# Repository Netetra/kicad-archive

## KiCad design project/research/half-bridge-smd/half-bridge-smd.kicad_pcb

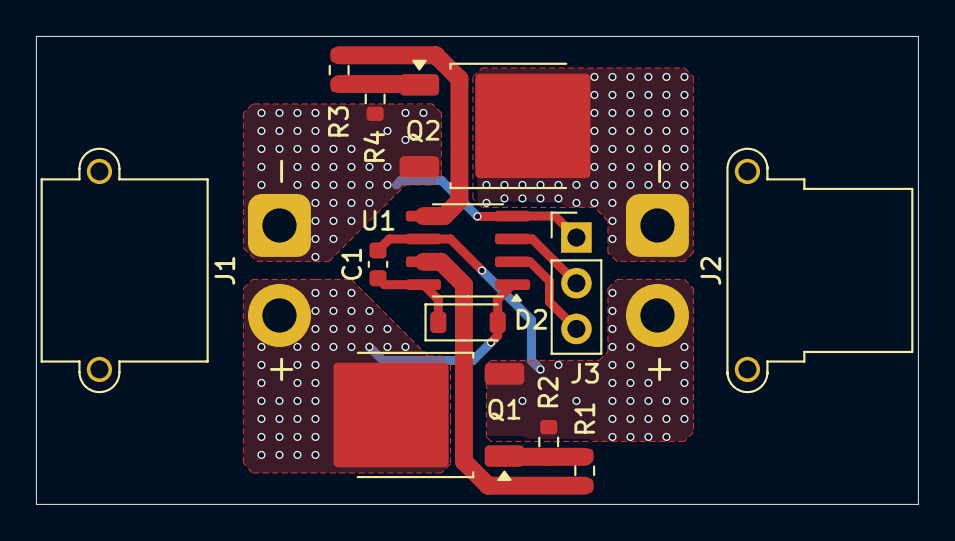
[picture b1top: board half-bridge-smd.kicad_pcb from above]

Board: 2 copper layers, 49.0 x 26.0 mm, 12 parts (0 on the bottom side), 11 nets.

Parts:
C1: 0.1uF; C_0603_1608Metric
D2: 1N4148W; D_SOD-123
J1: Power; AMASS_XT30PW-M_1x02_P2.50mm_Horizontal
J2: Output; AMASS_XT30PW-F_1x02_P2.50mm_Horizontal
J3: Input; PinHeader_1x03_P2.54mm_Vertical
Q1, Q2: TK25S06N1L; TO-252-2
R1, R3: 10Ω; R_0603_1608Metric
R2, R4: 10kΩ; R_0603_1608Metric
U1: IR2302; SOIC-8_3.9x4.9mm_P1.27mm

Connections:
+12V: D2.2 (A), J1.2, Q1.2 (D), U1.1 (VCC)
GND: J1.1, J3.1, Q2.3 (S), R4.2, U1.4 (COM)
unnamed: C1.1, D2.1 (K), U1.8 (VB)
unnamed: J2.1, Q2.2 (D)
unnamed: C1.2, J2.2, Q1.3 (S), R2.2, U1.6 (VS)
unnamed: J3.2, U1.3 (~SD)
unnamed: J3.3, U1.2 (IN)
unnamed: Q1.1 (G), R1.2, R2.1
unnamed: Q2.1 (G), R3.2, R4.1
unnamed: R1.1, U1.7 (HO)
unnamed: R3.1, U1.5 (LO)

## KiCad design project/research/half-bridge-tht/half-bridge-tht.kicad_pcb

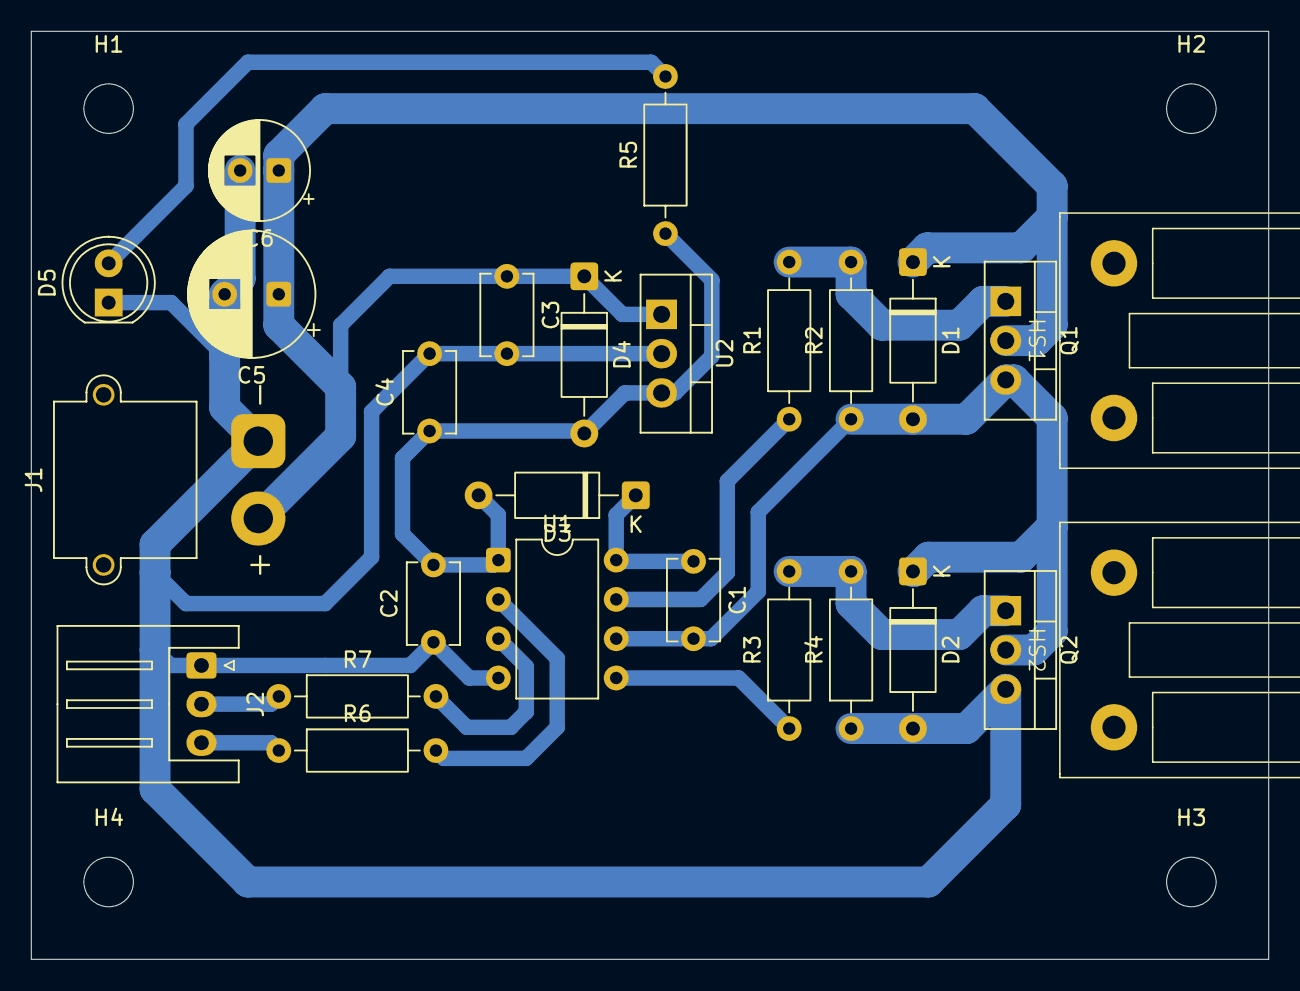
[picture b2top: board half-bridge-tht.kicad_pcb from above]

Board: 2 copper layers, 80.0 x 60.0 mm, 30 parts (0 on the bottom side), 14 nets.

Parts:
C1: 1uF; C_Disc_D5.1mm_W3.2mm_P5.00mm
C2, C4: 0.1uF; C_Disc_D5.1mm_W3.2mm_P5.00mm
C3: 0.47uF; C_Disc_D5.1mm_W3.2mm_P5.00mm
C5: 100uF; CP_Radial_D8.0mm_P3.50mm
C6: 47uF; CP_Radial_D6.3mm_P2.50mm
D1, D2, D3, D4: D; D_A-405_P10.16mm_Horizontal
D5: LED; LED_D5.0mm
H1, H2, H3, H4: MountingHole; MountingHole_3.2mm_M3
HS1, HS2: Heatsink; 16PB017
J1: Power; AMASS_XT30PW-M_1x02_P2.50mm_Horizontal
J2: Input; JST_XH_S3B-XH-A_1x03_P2.50mm_Horizontal
Q1, Q2: NMOS; TO-220-3_Vertical
R1, R3: 10Ω; R_Axial_DIN0207_L6.3mm_D2.5mm_P10.16mm_Horizontal
R2, R4, R5: 10kΩ; R_Axial_DIN0207_L6.3mm_D2.5mm_P10.16mm_Horizontal
R6, R7: 1kΩ; R_Axial_DIN0207_L6.3mm_D2.5mm_P10.16mm_Horizontal
U1: IR2302; DIP-8_W7.62mm
U2: L7812; TO-220-3_Vertical

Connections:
+12V: C2.2, C4.1, D3.2 (A), D4.2 (A), R5.1, U1.1 (VCC), U2.3 (OUT)
+BATT: C3.1, C5.1, C6.1, D1.1 (K), D4.1 (K), J1.2, Q1.2 (D), U2.1 (IN)
GND: C2.1, C3.2, C4.2, C5.2, C6.2, D2.2 (A), D5.1 (K), J1.1, J2.1, Q2.3 (S), R4.1, U1.4 (COM), U2.2 (GND)
unnamed: C1.2, D1.2 (A), D2.1 (K), Q1.3 (S), Q2.2 (D), R2.1, U1.6 (VS)
unnamed: C1.1, D3.1 (K), U1.8 (VB)
unnamed: D5.2 (A), R5.2
unnamed: J2.2, R7.1
unnamed: J2.3, R6.1
unnamed: Q1.1 (G), R1.2, R2.2
unnamed: Q2.1 (G), R3.2, R4.2
unnamed: R1.1, U1.7 (HO)
unnamed: R6.2, U1.2 (IN)
unnamed: R3.1, U1.5 (LO)
unnamed: R7.2, U1.3 (~SD)

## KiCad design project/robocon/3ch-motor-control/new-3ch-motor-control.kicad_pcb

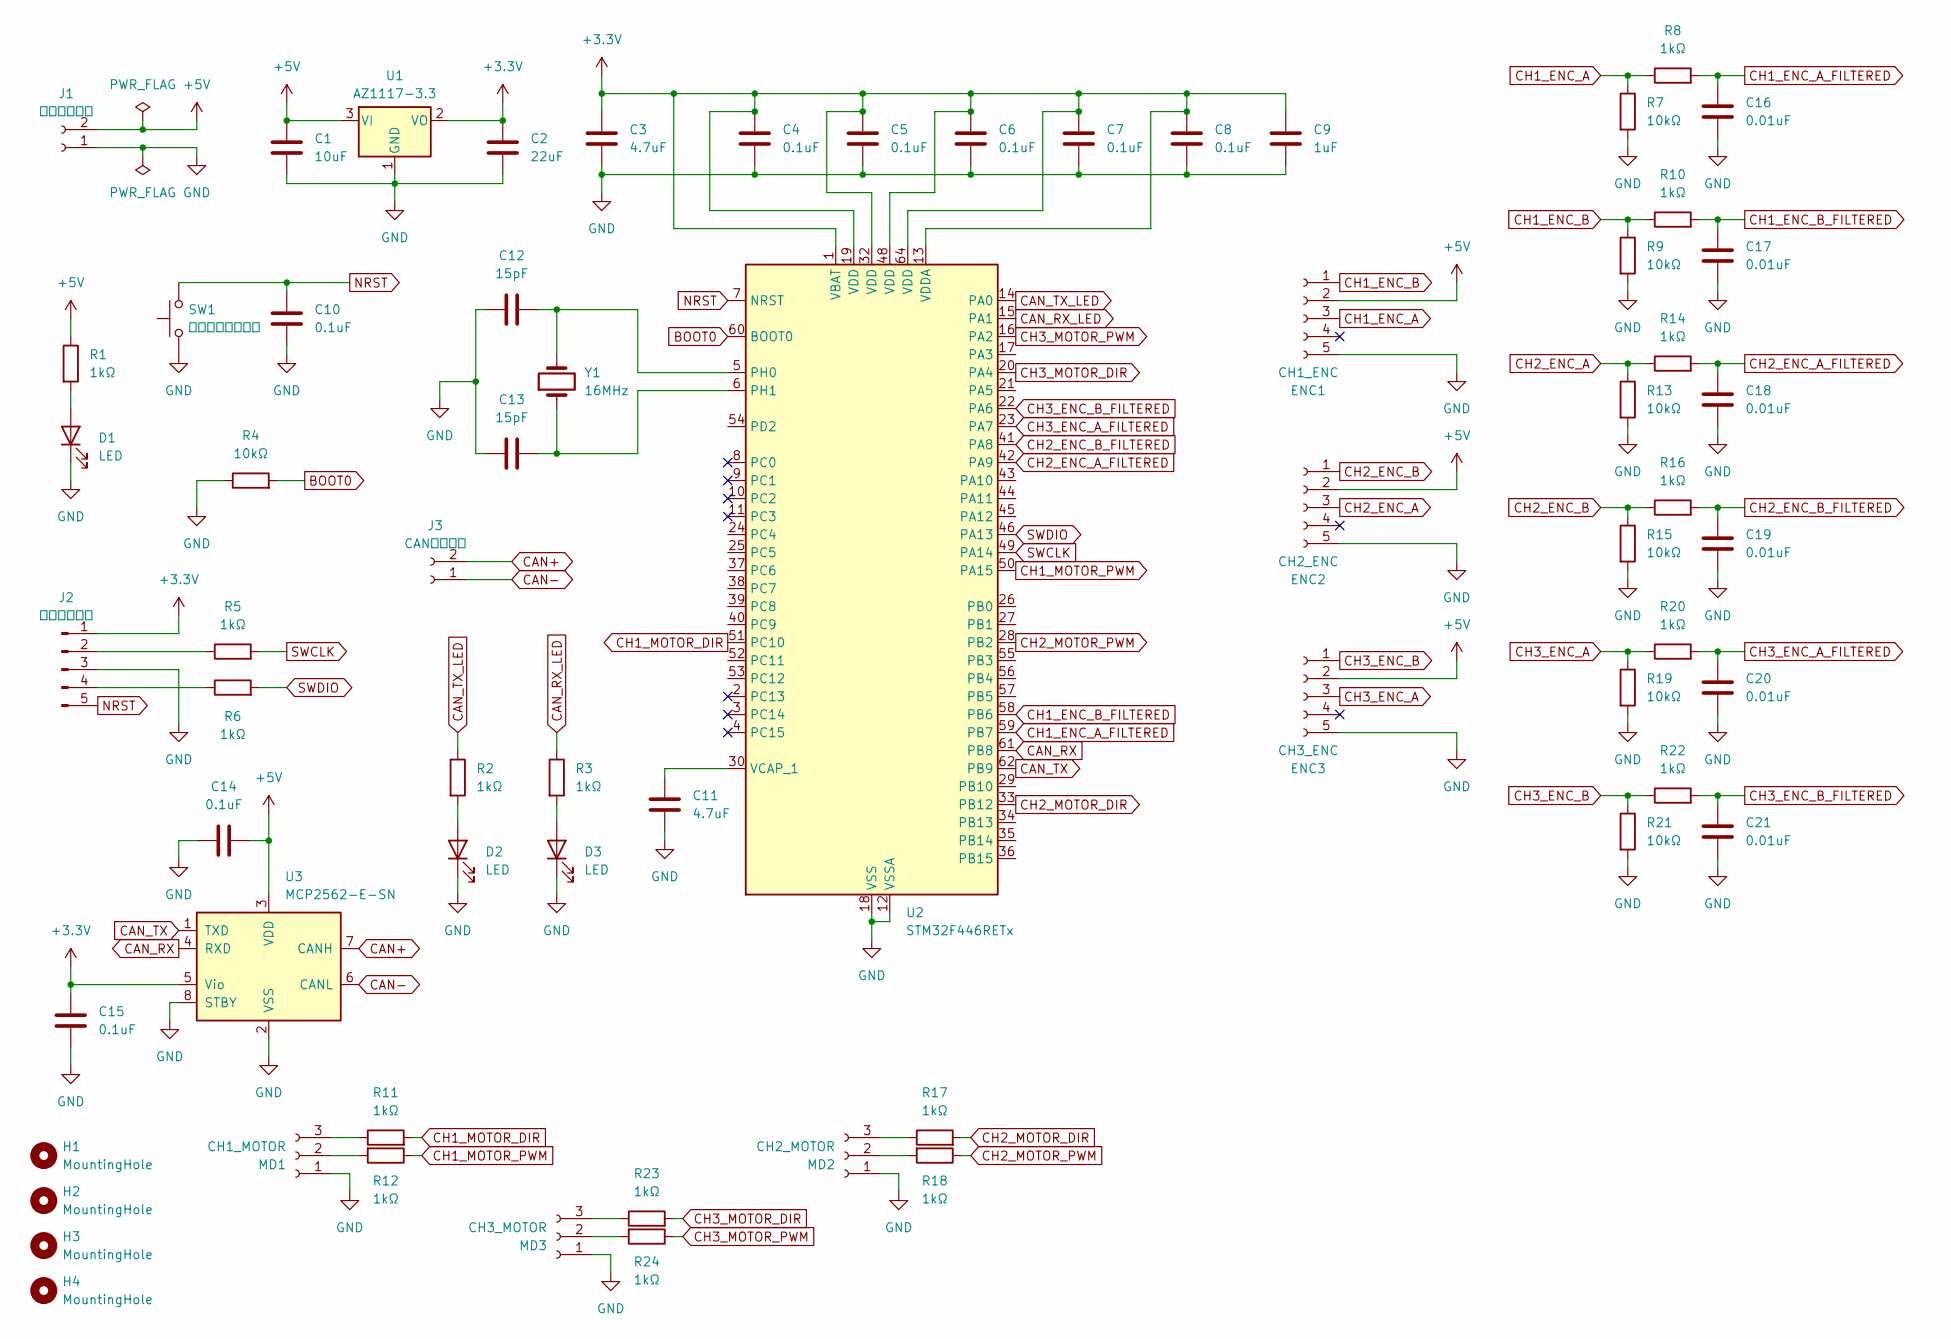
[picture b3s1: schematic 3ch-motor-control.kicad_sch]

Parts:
C1: 10uF; C_0603_1608Metric
C2: 22uF; C_0603_1608Metric
C3, C11: 4.7uF; C_0603_1608Metric
C4, C5, C6, C7, C8, C10, C14, C15: 0.1uF; C_0603_1608Metric
C9: 1uF; C_0603_1608Metric
C12, C13: 15pF; C_0603_1608Metric
C16, C17, C18, C19, C20, C21: 0.01uF; C_0603_1608Metric
D1, D2, D3: LED; LED_0603_1608Metric
ENC1: CH1_ENC; JST_XH_S5B-XH-A_1x05_P2.50mm_Horizontal
ENC2: CH2_ENC; JST_XH_S5B-XH-A_1x05_P2.50mm_Horizontal
ENC3: CH3_ENC; JST_XH_S5B-XH-A_1x05_P2.50mm_Horizontal
H1, H2, H3, H4: MountingHole; MountingHole_3.2mm_M3
J1: 電源コネクタ; AMASS_XT30PW-M_1x02_P2.50mm_Horizontal
J2: デバッグ端子; PinSocket_1x05_P2.54mm_Horizontal
J3: CANコネクタ; JST_XH_S2B-XH-A_1x02_P2.50mm_Horizontal
MD1: CH1_MOTOR; JST_XH_S3B-XH-A_1x03_P2.50mm_Horizontal
MD2: CH2_MOTOR; JST_XH_S3B-XH-A_1x03_P2.50mm_Horizontal
MD3: CH3_MOTOR; JST_XH_S3B-XH-A_1x03_P2.50mm_Horizontal
R1, R2, R3, R5, R6, R8, R10, R11, R12, R14, R16, R17, R18, R20, R22, R23, R24: 1kΩ; R_0603_1608Metric
R4, R7, R9, R13, R15, R19, R21: 10kΩ; R_0603_1608Metric
SW1: リセットスイッチ; SW_PUSH_6mm_H5mm
U1: AZ1117-3.3; SOT-223-3_TabPin2
U2: STM32F446RETx; LQFP-64_10x10mm_P0.5mm
U3: MCP2562-E-SN; SOIC-8_3.9x4.9mm_P1.27mm
Y1: 16MHz; Crystal_HC49-4H_Vertical

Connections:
+3.3V: C2.1, C3.1, C4.1, C5.1, C6.1, C7.1, C8.1, C9.1, C15.1, J2.1, U1.2 (VO), U2.1 (VBAT), U2.13 (VDDA), U2.19 (VDD), U2.32 (VDD), U2.48 (VDD), U2.64 (VDD), U3.5 (Vio)
+5V: C1.1, C14.2, ENC1.2, ENC2.2, ENC3.2, J1.2, R1.1, U1.3 (VI), U3.3 (VDD)
BOOT0: R4.2, U2.60 (BOOT0)
CAN+: J3.2, U3.7 (CANH)
CAN-: J3.1, U3.6 (CANL)
CAN_RX: U2.61 (PB8), U3.4 (RXD)
CAN_RX_LED: R3.1, U2.15 (PA1)
CAN_TX: U2.62 (PB9), U3.1 (TXD)
CAN_TX_LED: R2.1, U2.14 (PA0)
CH1_ENC_A: ENC1.3, R7.1, R8.1
CH1_ENC_A_FILTERED: C16.2, R8.2, U2.59 (PB7)
CH1_ENC_B: ENC1.1, R9.1, R10.1
CH1_ENC_B_FILTERED: C17.2, R10.2, U2.58 (PB6)
CH1_MOTOR_DIR: R11.2, U2.51 (PC10)
CH1_MOTOR_PWM: R12.1, U2.50 (PA15)
CH2_ENC_A: ENC2.3, R13.1, R14.1
CH2_ENC_A_FILTERED: C18.2, R14.2, U2.42 (PA9)
CH2_ENC_B: ENC2.1, R15.1, R16.1
CH2_ENC_B_FILTERED: C19.2, R16.2, U2.41 (PA8)
CH2_MOTOR_DIR: R17.2, U2.33 (PB12)
CH2_MOTOR_PWM: R18.1, U2.28 (PB2)
CH3_ENC_A: ENC3.3, R19.1, R20.1
CH3_ENC_A_FILTERED: C20.2, R20.2, U2.23 (PA7)
CH3_ENC_B: ENC3.1, R21.1, R22.1
CH3_ENC_B_FILTERED: C21.2, R22.2, U2.22 (PA6)
CH3_MOTOR_DIR: R23.2, U2.20 (PA4)
CH3_MOTOR_PWM: R24.1, U2.16 (PA2)
GND: C1.2, C2.2, C3.2, C4.2, C5.2, C6.2, C7.2, C8.2, C9.2, C10.2, C11.1, C12.1, C13.1, C14.1, C15.2, C16.1, C17.1, C18.1, C19.1, C20.1, C21.1, D1.1 (K), D2.1 (K), D3.1 (K), ENC1.5, ENC2.5, ENC3.5, J1.1, J2.3, MD1.1, MD2.1, MD3.1, R4.1, R7.2, R9.2, R13.2, R15.2, R19.2, R21.2, SW1.1, U1.1 (GND), U2.12 (VSSA), U2.18 (VSS), U2.31 (VSS), U2.47 (VSS), U2.63 (VSS), U3.2 (VSS), U3.8 (STBY)
NRST: C10.1, J2.5, SW1.2, U2.7 (NRST)
unnamed: D1.2 (A), R1.2
unnamed: D2.2 (A), R2.2
unnamed: D3.2 (A), R3.2
unnamed: J2.2, R5.1
unnamed: J2.4, R6.1
unnamed: MD1.2, R12.2
unnamed: MD1.3, R11.1
unnamed: MD2.2, R18.2
unnamed: MD2.3, R17.1
unnamed: MD3.2, R24.2
unnamed: MD3.3, R23.1
unnamed: C12.2, U2.5 (PH0), Y1.2
unnamed: C13.2, U2.6 (PH1), Y1.1
unnamed: C11.2, U2.30 (VCAP_1)
SWCLK: R5.2, U2.49 (PA14)
SWDIO: R6.2, U2.46 (PA13)

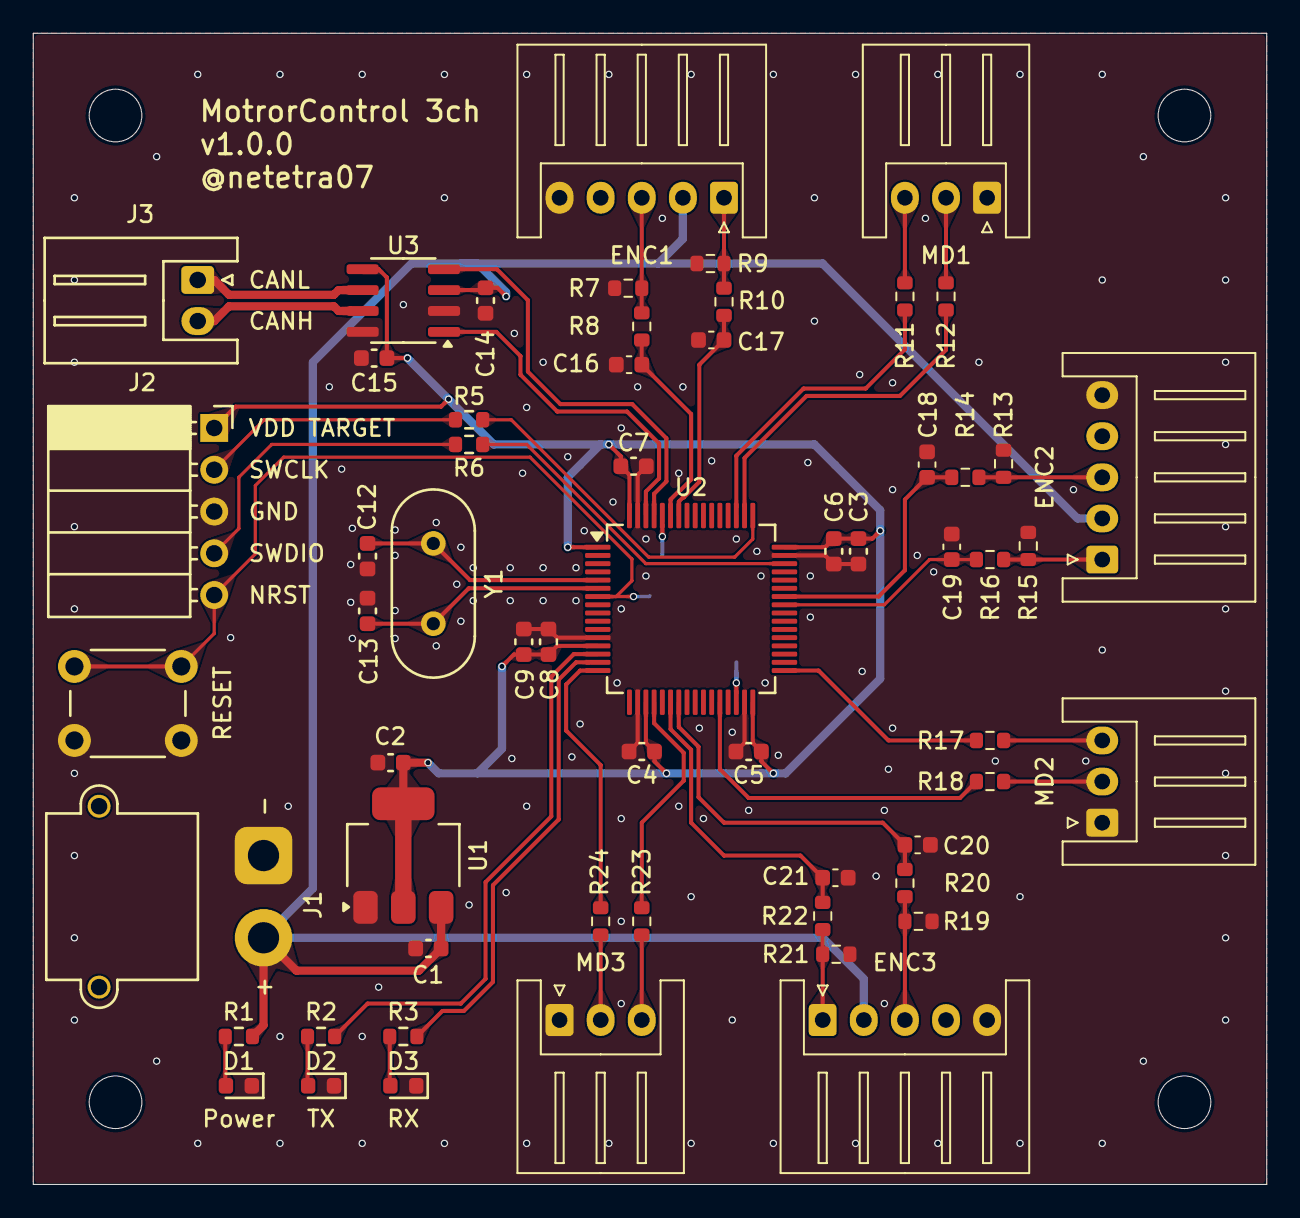
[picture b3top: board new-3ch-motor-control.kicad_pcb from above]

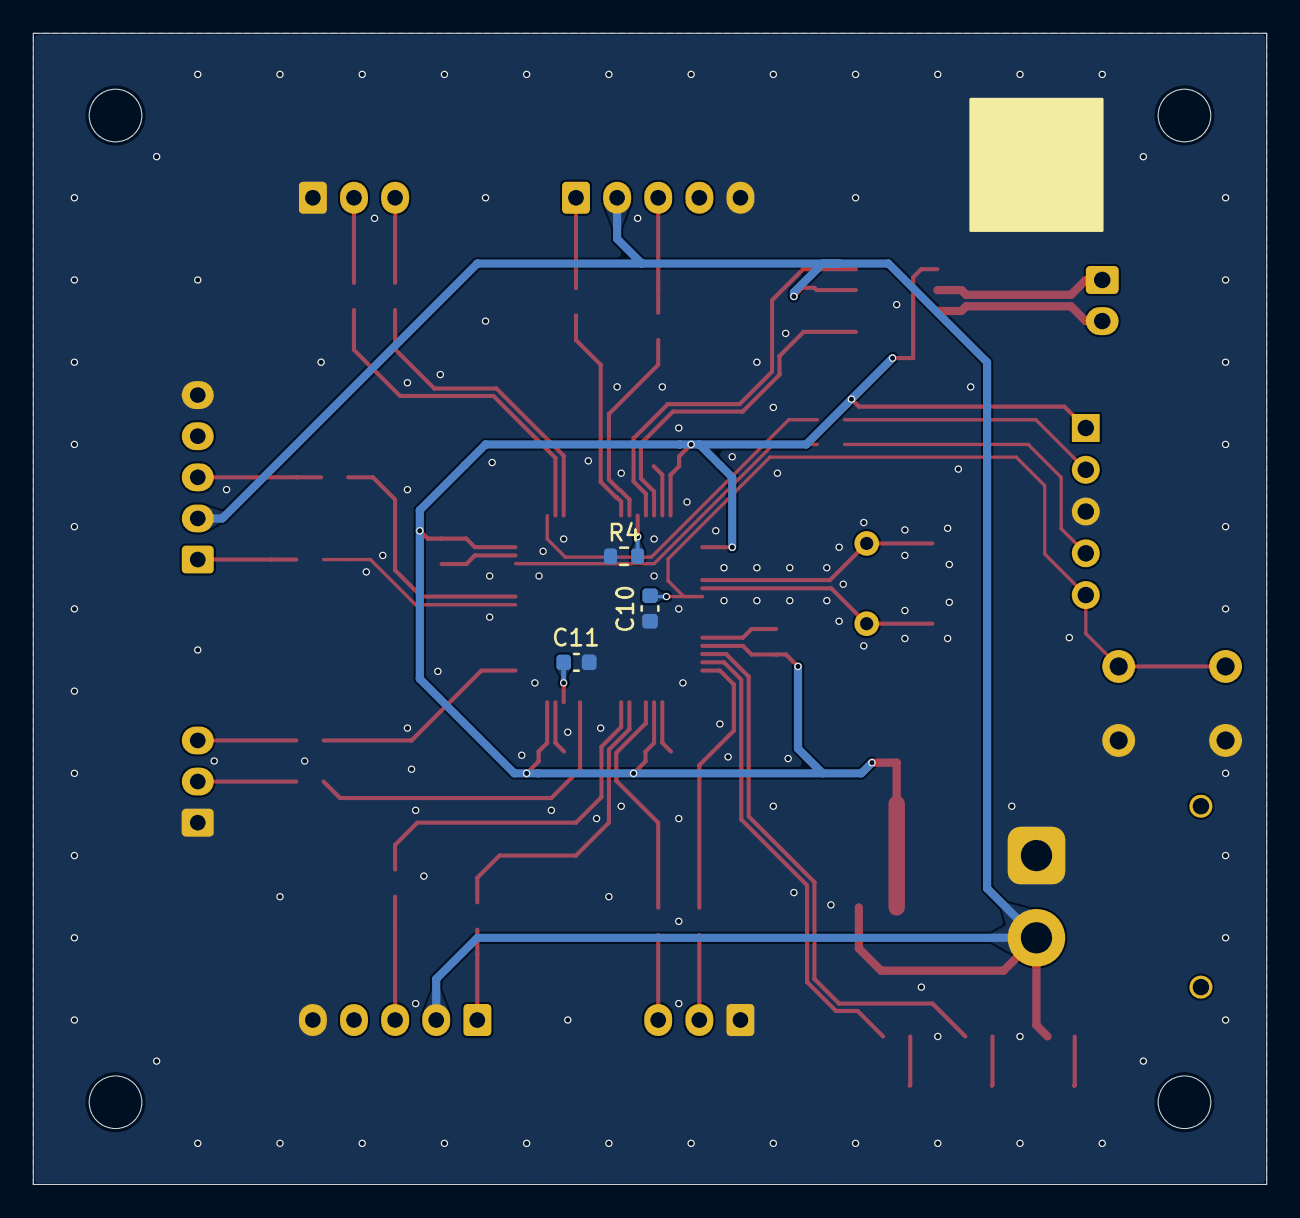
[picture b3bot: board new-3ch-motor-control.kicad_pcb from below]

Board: 2 copper layers, 75.0 x 70.0 mm, 66 parts (3 on the bottom side), 45 nets.

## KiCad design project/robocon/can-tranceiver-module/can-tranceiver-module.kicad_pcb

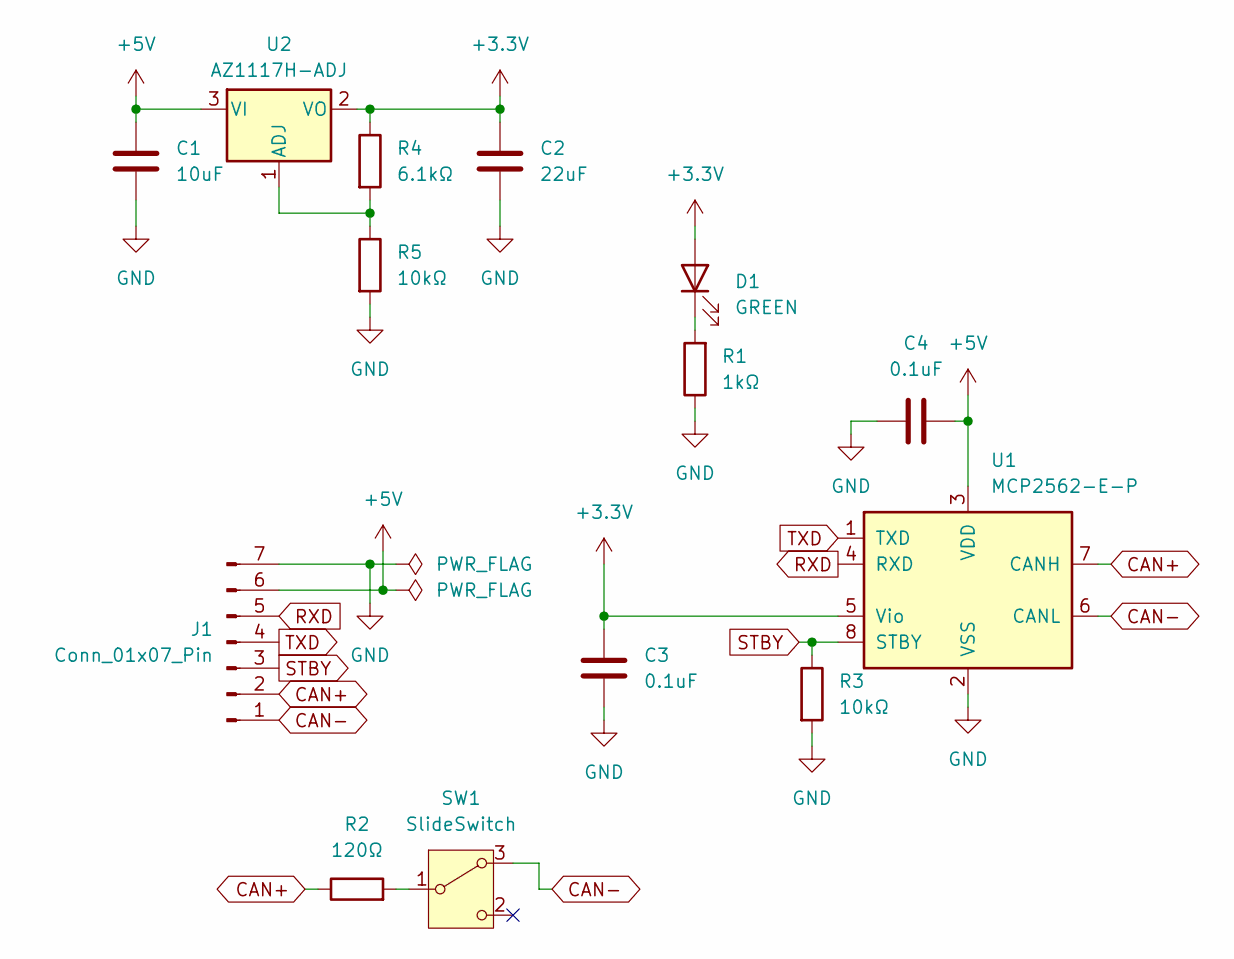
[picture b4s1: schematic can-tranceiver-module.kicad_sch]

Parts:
C1: 10uF; C_Disc_D5.1mm_W3.2mm_P5.00mm
C2: 22uF; C_Disc_D5.1mm_W3.2mm_P5.00mm
C3, C4: 0.1uF; C_Disc_D5.1mm_W3.2mm_P5.00mm
D1: GREEN; LED_D5.0mm
J1: Conn_01x07_Pin; PinHeader_1x07_P2.54mm_Horizontal
R1: 1kΩ; R_Axial_DIN0207_L6.3mm_D2.5mm_P10.16mm_Horizontal
R2: 120Ω; R_Axial_DIN0207_L6.3mm_D2.5mm_P10.16mm_Horizontal
R3: 10kΩ; R_Axial_DIN0207_L6.3mm_D2.5mm_P10.16mm_Horizontal
R4: 6.1kΩ; R_0603_1608Metric
R5: 10kΩ; R_0603_1608Metric
SW1: SlideSwitch; SW_Slide-03_Wuerth-WS-SLTV_10x2.5x6.4_P2.54mm
U1: MCP2562-E-P; DIP-8_W7.62mm
U2: AZ1117H-ADJ; SOT-223-3_TabPin2

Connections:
+3.3V: C2.1, C3.1, D1.2 (A), R4.1, U1.5 (Vio), U2.2 (VO)
+5V: C1.1, C4.2, J1.6, U1.3 (VDD), U2.3 (VI)
CAN+: J1.2, R2.1, U1.7 (CANH)
CAN-: J1.1, SW1.3 (A), U1.6 (CANL)
GND: C1.2, C2.2, C3.2, C4.1, J1.7, R1.1, R3.2, R5.2, U1.2 (VSS)
unnamed: D1.1 (K), R1.2
unnamed: R2.2, SW1.1 (B)
unnamed: R4.2, R5.1, U2.1 (ADJ)
RXD: J1.5, U1.4 (RXD)
STBY: J1.3, R3.1, U1.8 (STBY)
TXD: J1.4, U1.1 (TXD)

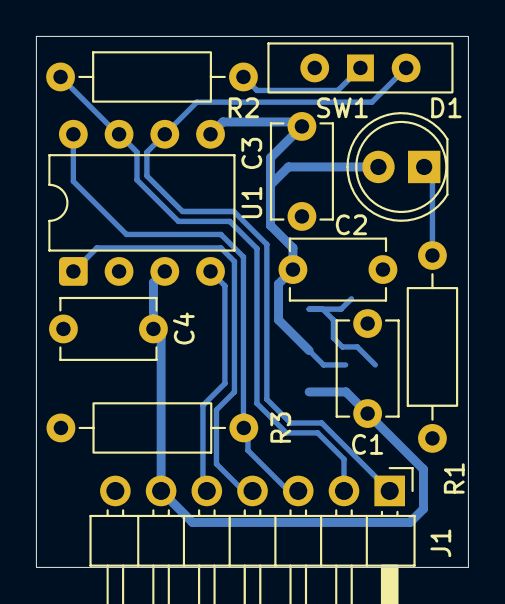
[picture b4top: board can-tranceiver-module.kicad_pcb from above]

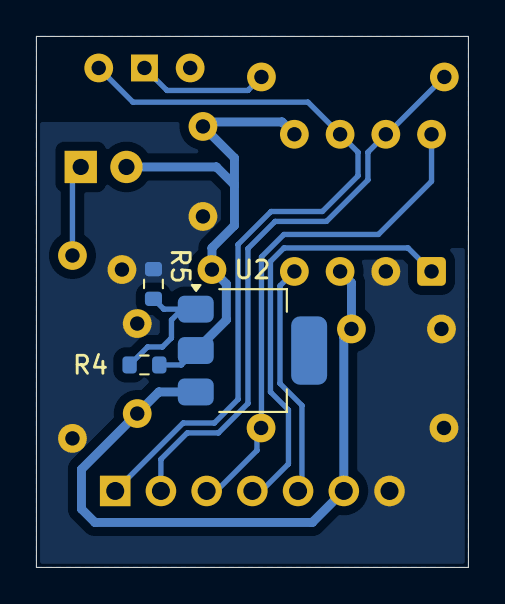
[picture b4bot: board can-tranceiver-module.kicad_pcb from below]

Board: 2 copper layers, 24.0 x 29.5 mm, 14 parts (3 on the bottom side), 11 nets.

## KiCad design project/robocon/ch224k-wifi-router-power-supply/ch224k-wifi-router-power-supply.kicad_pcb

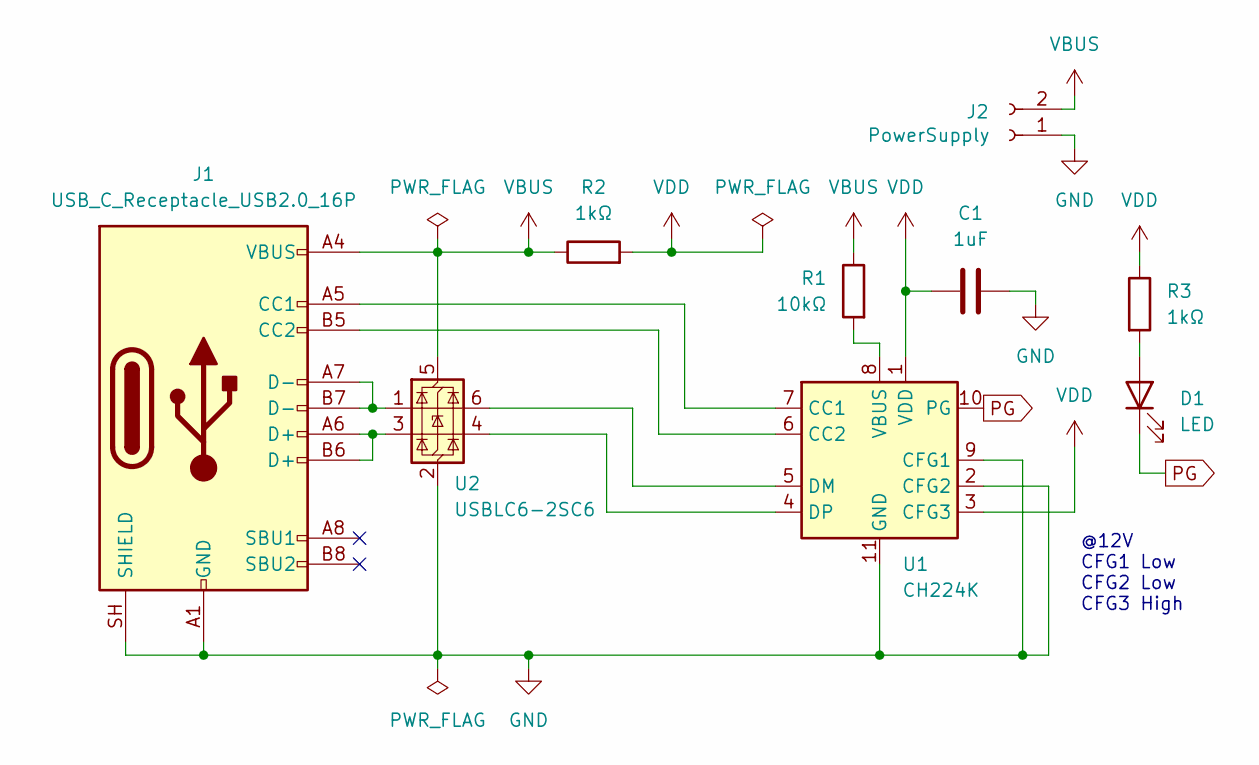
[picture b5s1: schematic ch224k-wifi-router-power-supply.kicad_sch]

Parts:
C1: 1uF; C_0805_2012Metric
D1: LED; LED_0603_1608Metric
J1: USB_C_Receptacle_USB2.0_16P; USB_C_Receptacle_HRO_TYPE-C-31-M-12
J2: PowerSupply; AMASS_XT30PW-F_1x02_P2.50mm_Horizontal
R1: 10kΩ; R_0603_1608Metric
R2: 1kΩ; R_2512_6332Metric
R3: 1kΩ; R_0603_1608Metric
U1: CH224K; SSOP-10-1EP_3.9x4.9mm_P1mm_EP2.1x3.3mm
U2: USBLC6-2SC6; SOT-23-6

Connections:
GND: C1.2, J1.A1 (GND), J1.A12 (GND), J1.B1 (GND), J1.B12 (GND), J1.SH (SHIELD), J2.1, U1.2 (CFG2), U1.9 (CFG1), U1.11 (GND), U2.2 (GND)
unnamed: D1.2 (A), R3.2
unnamed: J1.A5 (CC1), U1.7 (CC1)
unnamed: J1.B5 (CC2), U1.6 (CC2)
unnamed: J1.A6 (D+), J1.B6 (D+), U2.3 (I/O2)
unnamed: J1.A7 (D-), J1.B7 (D-), U2.1 (I/O1)
unnamed: U1.5 (DM), U2.6 (I/O1)
unnamed: U1.4 (DP), U2.4 (I/O2)
unnamed: R1.2, U1.8 (VBUS)
PG: D1.1 (K), U1.10 (PG)
VBUS: J1.A4 (VBUS), J1.A9 (VBUS), J1.B4 (VBUS), J1.B9 (VBUS), J2.2, R1.1, R2.1, U2.5 (VBUS)
VDD: C1.1, R2.2, R3.1, U1.1 (VDD), U1.3 (CFG3)

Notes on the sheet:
@12V CFG1 Low CFG2 Low CFG3 High

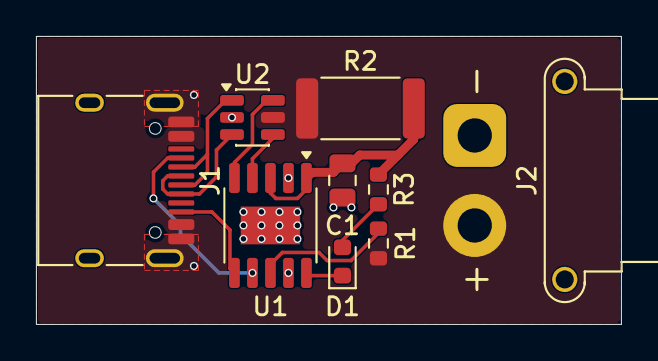
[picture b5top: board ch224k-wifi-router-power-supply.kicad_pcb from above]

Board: 2 copper layers, 32.5 x 16.0 mm, 9 parts (0 on the bottom side), 12 nets.

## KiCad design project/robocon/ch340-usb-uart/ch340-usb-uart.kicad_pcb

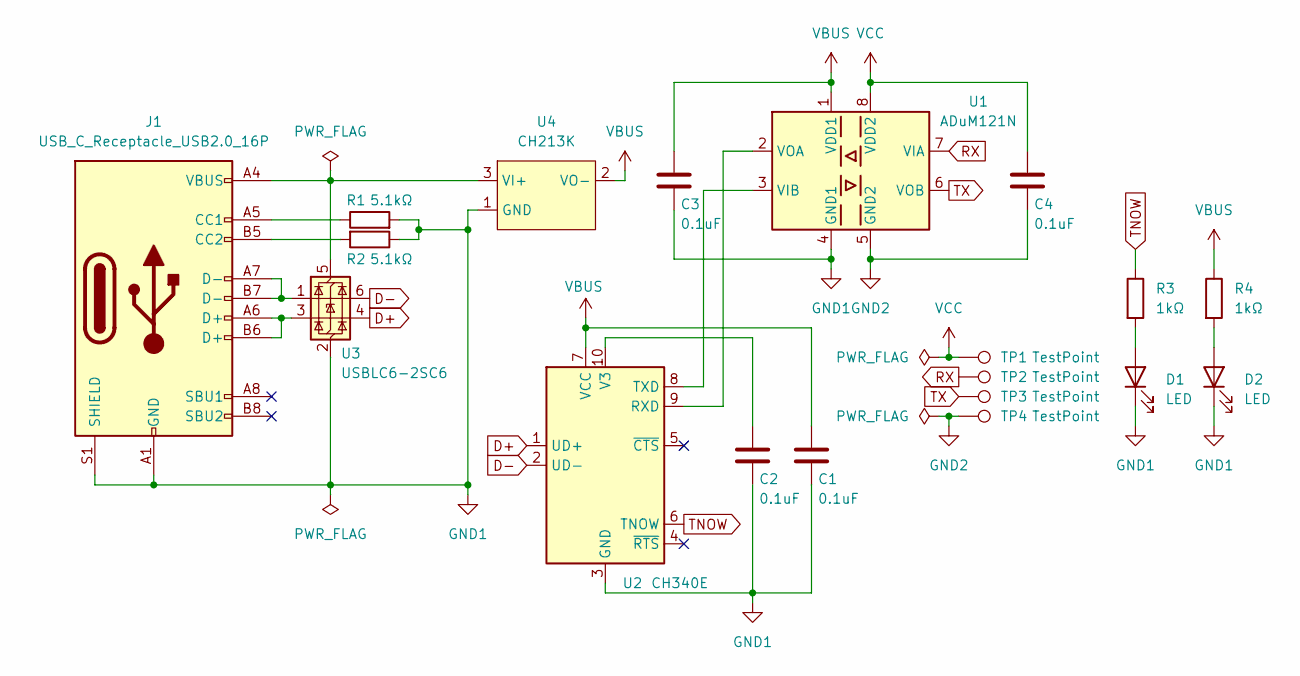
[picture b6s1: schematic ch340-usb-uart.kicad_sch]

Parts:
C1, C2, C3, C4: 0.1uF; C_0603_1608Metric
D1, D2: LED; LED_0603_1608Metric
J1: USB_C_Receptacle_USB2.0_16P; USB_C_Receptacle_HRO_TYPE-C-31-M-12
R1, R2: 5.1kΩ; R_0603_1608Metric
R3, R4: 1kΩ; R_0603_1608Metric
TP1, TP2, TP3, TP4: TestPoint; TestPoint_Keystone_5015_Micro_Mini
U1: ADuM121N; SOIC-8_3.9x4.9mm_P1.27mm
U2: CH340E; MSOP-10_3x3mm_P0.5mm
U3: USBLC6-2SC6; SOT-23-6
U4: CH213K; SOT-23-3

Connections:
D+: U2.1 (UD+), U3.4 (I/O2)
D-: U2.2 (UD-), U3.6 (I/O1)
GND1: C1.2, C2.2, C3.2, D1.1 (K), D2.1 (K), J1.A1 (GND), J1.A12 (GND), J1.B1 (GND), J1.B12 (GND), J1.S1 (SHIELD), R1.2, R2.1, U1.4 (GND1), U2.3 (GND), U3.2 (GND), U4.1 (GND)
GND2: C4.2, TP4.1, U1.5 (GND2)
unnamed: D1.2 (A), R3.2
unnamed: D2.2 (A), R4.2
unnamed: J1.A5 (CC1), R1.1
unnamed: J1.B5 (CC2), R2.2
unnamed: J1.A6 (D+), J1.B6 (D+), U3.3 (I/O2)
unnamed: J1.A7 (D-), J1.B7 (D-), U3.1 (I/O1)
unnamed: U1.3 (VIB), U2.8 (TXD)
unnamed: U1.2 (VOA), U2.9 (RXD)
unnamed: C2.1, U2.10 (V3)
unnamed: J1.A4 (VBUS), J1.A9 (VBUS), J1.B4 (VBUS), J1.B9 (VBUS), U3.5 (VBUS), U4.3 (VI+)
RX: TP2.1, U1.7 (VIA)
TNOW: R3.1, U2.6 (TNOW)
TX: TP3.1, U1.6 (VOB)
VBUS: C1.1, C3.1, R4.1, U1.1 (VDD1), U2.7 (VCC), U4.2 (VO-)
VCC: C4.1, TP1.1, U1.8 (VDD2)

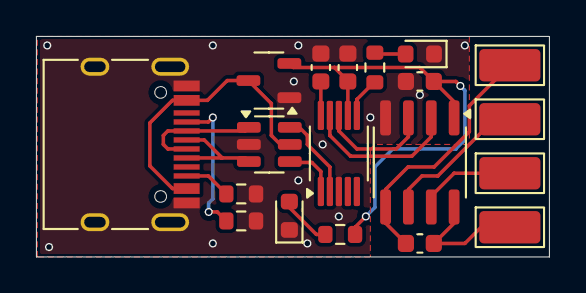
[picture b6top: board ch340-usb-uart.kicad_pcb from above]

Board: 2 copper layers, 28.5 x 12.2 mm, 19 parts (0 on the bottom side), 19 nets.

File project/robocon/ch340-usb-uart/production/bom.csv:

Designator,Footprint,Quantity,Value,LCSC Part #
"C1_24, C1_23, C1_22, C1_21, C1_20, C1_19, C1_18, C1_17, C1_16, C1_15, C1_14, C1_13, C1_12, C1_11, C1_10, C1_9, C1_8, C1_7, C1_6, C1_5, C1_4, C1_3, C1_2, C1, C2_24, C2_23, C2_22, C2_21, C2_20, C2_19, C2_18, C2_17, C2_16, C2_15, C2_14, C2_13, C2_12, C2_11, C2_10, C2_9, C2_8, C2_7, C2_6, C2_5, C2_4, C2_3, C2_2, C2, C3_24, C3_23, C3_22, C3_21, C3_20, C3_19, C3_18, C3_17, C3_16, C3_15, C3_14, C3_13, C3_12, C3_11, C3_10, C3_9, C3_8, C3_7, C3_6, C3_5, C3_4, C3_3, C3_2, C3, C4_24, C4_23, C4_22, C4_21, C4_20, C4_19, C4_18, C4_17, C4_16, C4_15, C4_14, C4_13, C4_12, C4_11, C4_10, C4_9, C4_8, C4_7, C4_6, C4_5, C4_4, C4_3, C4_2, C4",0603,96,0.1uF,
"D1_24, D1_23, D1_22, D1_21, D1_20, D1_19, D1_18, D1_17, D1_16, D1_15, D1_14, D1_13, D1_12, D1_11, D1_10, D1_9, D1_8, D1_7, D1_6, D1_5, D1_4, D1_3, D1_2, D1, D2_24, D2_23, D2_22, D2_21, D2_20, D2_19, D2_18, D2_17, D2_16, D2_15, D2_14, D2_13, D2_12, D2_11, D2_10, D2_9, D2_8, D2_7, D2_6, D2_5, D2_4, D2_3, D2_2, D2",0603,48,LED,
"J1_24, J1_23, J1_22, J1_21, J1_20, J1_19, J1_18, J1_17, J1_16, J1_15, J1_14, J1_13, J1_12, J1_11, J1_10, J1_9, J1_8, J1_7, J1_6, J1_5, J1_4, J1_3, J1_2, J1",USB_C_Receptacle_HRO_TYPE-C-31-M-12,24,USB_C_Receptacle_USB2.0_16P,
"R1_24, R1_23, R1_22, R1_21, R1_20, R1_19, R1_18, R1_17, R1_16, R1_15, R1_14, R1_13, R1_12, R1_11, R1_10, R1_9, R1_8, R1_7, R1_6, R1_5, R1_4, R1_3, R1_2, R1, R2_24, R2_23, R2_22, R2_21, R2_20, R2_19, R2_18, R2_17, R2_16, R2_15, R2_14, R2_13, R2_12, R2_11, R2_10, R2_9, R2_8, R2_7, R2_6, R2_5, R2_4, R2_3, R2_2, R2",0603,48,5.1kΩ,
"R3_24, R3_23, R3_22, R3_21, R3_20, R3_19, R3_18, R3_17, R3_16, R3_15, R3_14, R3_13, R3_12, R3_11, R3_10, R3_9, R3_8, R3_7, R3_6, R3_5, R3_4, R3_3, R3_2, R3, R4_24, R4_23, R4_22, R4_21, R4_20, R4_19, R4_18, R4_17, R4_16, R4_15, R4_14, R4_13, R4_12, R4_11, R4_10, R4_9, R4_8, R4_7, R4_6, R4_5, R4_4, R4_3, R4_2, R4",0603,48,1kΩ,
"TP1_24, TP1_23, TP1_22, TP1_21, TP1_20, TP1_19, TP1_18, TP1_17, TP1_16, TP1_15, TP1_14, TP1_13, TP1_12, TP1_11, TP1_10, TP1_9, TP1_8, TP1_7, TP1_6, TP1_5, TP1_4, TP1_3, TP1_2, TP1, TP2_24, TP2_23, TP2_22, TP2_21, TP2_20, TP2_19, TP2_18, TP2_17, TP2_16, TP2_15, TP2_14, TP2_13, TP2_12, TP2_11, TP2_10, TP2_9, TP2_8, TP2_7, TP2_6, TP2_5, TP2_4, TP2_3, TP2_2, TP2, TP3_24, TP3_23, TP3_22, TP3_21, TP3_20, TP3_19, TP3_18, TP3_17, TP3_16, TP3_15, TP3_14, TP3_13, TP3_12, TP3_11, TP3_10, TP3_9, TP3_8, TP3_7, TP3_6, TP3_5, TP3_4, TP3_3, TP3_2, TP3, TP4_24, TP4_23, TP4_22, TP4_21, TP4_20, TP4_19, TP4_18, TP4_17, TP4_16, TP4_15, TP4_14, TP4_13, TP4_12, TP4_11, TP4_10, TP4_9, TP4_8, TP4_7, TP4_6, TP4_5, TP4_4, TP4_3, TP4_2, TP4",TestPoint_Keystone_5015_Micro_Mini,96,TestPoint,
"U1_24, U1_23, U1_22, U1_21, U1_20, U1_19, U1_18, U1_17, U1_16, U1_15, U1_14, U1_13, U1_12, U1_11, U1_10, U1_9, U1_8, U1_7, U1_6, U1_5, U1_4, U1_3, U1_2, U1",SOIC-8_3.9x4.9mm_P1.27mm,24,ADuM121N,
"U2_24, U2_23, U2_22, U2_21, U2_20, U2_19, U2_18, U2_17, U2_16, U2_15, U2_14, U2_13, U2_12, U2_11, U2_10, U2_9, U2_8, U2_7, U2_6, U2_5, U2_4, U2_3, U2_2, U2",MSOP-10_3x3mm_P0.5mm,24,CH340E,
"U3_24, U3_23, U3_22, U3_21, U3_20, U3_19, U3_18, U3_17, U3_16, U3_15, U3_14, U3_13, U3_12, U3_11, U3_10, U3_9, U3_8, U3_7, U3_6, U3_5, U3_4, U3_3, U3_2, U3",SOT-23-6,24,USBLC6-2SC6,
"U4_24, U4_23, U4_22, U4_21, U4_20, U4_19, U4_18, U4_17, U4_16, U4_15, U4_14, U4_13, U4_12, U4_11, U4_10, U4_9, U4_8, U4_7, U4_6, U4_5, U4_4, U4_3, U4_2, U4",SOT-23-3,24,CH213K,
